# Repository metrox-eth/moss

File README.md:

# MOSS

Cleaner streets, one maker at a time.

> **MOSS kits are coming soon on [TNKR](https://tnkr.ai/).**
> Skip printing and sourcing the parts yourself. **[Join the waitlist →](https://ak4khuvxkya.typeform.com/to/qaKmXNME)** to be notified when kits are available.

**[Build guide](https://www.showrobotics.ai/moss/build/) · [Print parts](https://www.showrobotics.ai/moss/build/#print) · [Bill of materials](BOM.md) · [Download CAD, STL & 3MF](https://github.com/metrox-eth/moss/releases/download/v0.6-r92/MOSS_R92_Mechanical_20261109.zip) · [Software setup](Software.md)**

MOSS is a small litter-picking rover you print and build yourself: a tracked base, a bin on top, an arm derived from the SO-101 with a parallel gripper. It is built in public, with hardware files available for noncommercial builds and improvements.

**Where it stands.** The physical rover drives and demonstrates pick-and-drop motions. Autonomous litter picking and the full field test are not yet demonstrated. The V0.6 / R92 CAD, STL files, BOM and assembly guide are now available.

## Build options

**Base assembly: about $460 in parts.** Includes the chassis and tracks, arm and gripper, motors, servos, control electronics, power system, wrist camera, 2D lidar, wiring and filament. **Only the computer and navigation camera are additional.**

**Choose ONE of the three options below, depending on your budget.** They are alternative computer + navigation-camera configurations for the same rover base. You do not need to buy all three.

| Option | Computer + navigation camera | Additional cost (USD) | Estimated rover total, including the $460 base (USD) |
|---|---|---:|---:|
| **Option 1: higher budget** | Jetson Orin Nano Super + RealSense D455 | about $930 | **about $1,390** |
| **Option 2: mid-range budget** | Raspberry Pi 5 + Hailo AI HAT + Orbbec Gemini 2 | about $740 | **about $1,200** |
| **Option 3: lowest budget, experimental** | Orange Pi Zero 3W (6 GB, $60) + MightyCam ($80) | about $140 | **about $600** |

**Option 1 offers the most computing headroom for the autonomy software being developed.** It does not guarantee autonomous operation: autonomous litter collection has not yet been demonstrated on any of these configurations.

The goal is to bring as much of the stack as possible to smaller, lower-cost hardware. This work involves porting, optimizing and testing features progressively, and **it will take time**. Feature support will depend on what can be ported and validated on each hardware option.

**Option 3 is experimental for now.** Early Orange Pi + MightyCam bench tests are documented in the [experiment folder](experiments/orange-pi-mightycam/); the combination is not yet validated as a complete rover configuration. The [BOM](BOM.md) covers the established configurations.

## What it is made of

- Tracked base, two geared DC motors with encoders, printed TPU tracks, an ESP32-S3 driving the motors.
- A bin you empty by hand at the end of a run.
- An SO-101 arm (open source) with a NormaCore parallel-jaw gripper, widened to a 90 mm grip.
- Two cameras: a depth camera at the nose, a colour camera in the hand.
- A 2D lidar for navigation.
- Software: dimOS for teleop, recording, navigation and manipulation.

I pick up litter by hand on my walks. MOSS is the robot I want next to me doing the same. One less can on the ground.

## News

- 1 November 2026: **[MOSS CORE V0.7 updated](hardware/electronics/moss-core-v0.7/)** — black 82 × 79 mm board, vertical cable headers, larger underside connector labels, a 74 × 71 mm chassis mounting pattern and a new routing layout. Orange Pi assembly clearance and the matched KiCad/BOM/Gerber package are documented. The integrated power supply, current sensing and consolidated motor harness remain. First prototype, not built or tested yet.

- 30 October 2026: **[MOSS CORE V0.7 harness study](hardware/electronics/moss-core-v0.7/harness/)** — a short film, offline 3D viewer, cable routing and a hull prototype with integrated cable-tie mounts. An unbuilt packaging proposal, published for review.

- 28 October 2026: **[Build a custom 3S4P battery for MOSS](hardware/power/custom-3s4p-battery/)** — twelve EVE 21700 cells, illustrated assembly, wiring diagram and parts list. 20 Ah from the cell ratings, 910 g assembled; usable energy and collection runtime still to be measured.
- 27 October 2026: **[Orange Pi + MightyCam experiment](experiments/orange-pi-mightycam/)** — dimOS, YOLO on the NPU and a first memory/load test with simulated rover I/O. Code, cockpit image and the limits of this early bench demo.
- 27 October 2026: **[SO-101 dual-servo shoulder R2: complete upgrade guide](hardware/mechanical/dual-shoulder-r2/)** — editable CAD, two printable parts, screws, assembly, paired-servo setup and testing in one place.
- 24 October 2026: **BOM and print plates updated.** Hoco HB1 four-port hub, GameSir Nova 2 Lite controller, all 38 spacers on one plate, and one tensioner-slider reference (print four). [Updated package](https://github.com/metrox-eth/moss/releases/download/v0.6-r92/MOSS_R92_Mechanical_20261024.zip) · [Print plates](https://www.showrobotics.ai/moss/build/print-plates.html).
- 18 October 2026: **Ready-to-print plates are available.** [H2S: one-piece hull and cover](https://github.com/metrox-eth/moss/releases/download/v0.6-r92/MOSS_V06_R92_H2S_Print_Plates.3mf) or [P1 / P2: split hull and cover](https://github.com/metrox-eth/moss/releases/download/v0.6-r92/MOSS_V06_R92_256mm_Split_Print_Plates.3mf). The [updated package](https://github.com/metrox-eth/moss/releases/download/v0.6-r92/MOSS_R92_Mechanical_20261018.zip) includes both Jetson retaining tabs, grouped STLs with quantities, and both 3MF projects. [Choose your plates](https://www.showrobotics.ai/moss/build/print-plates.html).

- 16 October 2026: **V0.6 / R92 is available.** [Build guide](https://www.showrobotics.ai/moss/build/), [CAD & STL package](https://github.com/metrox-eth/moss/releases/tag/v0.6-r92) and [BOM](BOM.md). One-piece and two-piece hull/cover options, modular computer and camera carriers, and short assembly videos.

- 15 October 2026: [MOSS Core V1D routed PCB draft](hardware/electronics/moss-core-v1d/): integrated audio and switched motor/servo power, published for review. Untested and not approved for fabrication. [V1C critical erratum](hardware/electronics/moss-core-v1d/V1C_CRITICAL_ERRATA.txt): do not fabricate V1C.
- 14 October 2026: [CAD development with Codex](docs/cad-with-codex.md): more battery room, integrated audio, a slimmer hull, a P1S split-hull option and deeper track guides. Images and geometry checks; physical validation is next.
- 3 October 2026: V0.6 makes the hardware modular, Pi or Jetson, RealSense or Gemini. Waitlist open with Tnkr.
- 1 October 2026: V0.5, the release candidate for the open source CAD.
- 26 September 2026: arm and gripper mounted on the prototype.
- 22 September 2026: first drive.

## Friends

OpenAI (Codex Physical Builds), [PCBWay](https://www.pcbway.com/) (custom PCB prototyping), [Dimensional](https://x.com/dimensionalos) (dimOS), [NormaCore](https://x.com/norma_core_dev) (gripper), [Tnkr](https://x.com/tnkrdotai) (kits and guide), [Dirac Robotics](https://x.com/diracrobotics) (calibrated simulation), [microduck-lab](https://github.com/jonathanhawkins/microduck-lab) (reinforcement learning). We help each other.

## Supporters

People who put a spool of filament in the rover every month: [Richard Burton](https://github.com/ricburton). It goes into parts the same week. You can join them on [GitHub Sponsors](https://github.com/sponsors/metrox-eth).

## Simulation and autonomy, work in progress

The current **[MOSS V0.6 / R92 MuJoCo model](simulation/mujoco/)** lives in this repository, with its XML, meshes, viewer and tests. It includes the released assembly geometry, an articulated arm and coupled gripper, and an idealized base that can drive and turn. It runs locally without Jev or an API key. Start with the **[simulation guide](simulation/mujoco/README.md)** or **[model files](simulation/mujoco/model/)**.

This is a preliminary development model: traction, servo dynamics, camera geometry and sim-to-real accuracy remain uncalibrated. Dirac Robotics is helping build the calibrated simulation; Dimensional is working on a navigation arena, and microduck-lab is trying reinforcement learning. The earlier recorded Jev demonstration remains in [moss-jev](https://github.com/metrox-eth/moss-jev) as historical work.

## Come and build

Ask anything, tell us what we are doing wrong, it helps the next builder: [Discord](https://discord.com/invite/x2MeNmgveT). The build, as it happens: [@metrox_eth](https://x.com/metrox_eth). The story so far, in a few moments: [STORY.md](STORY.md). How data from many rovers gets pooled: [docs/data.md](docs/data.md).

## Safety

This is a prototype with a lithium battery and no certified protection. Put it on blocks for the first run. Build at your own risk.

## License

Code remains under Apache-2.0. From **1 November 2026**, the current distribution of MOSS-authored hardware designs is offered under **[CC BY-NC-SA 4.0](LICENSE-HARDWARE)**: attribution, noncommercial use and ShareAlike. Documentation and media remain under CC BY 4.0.

Earlier CERN-OHL-S-2.0 distributions retain the rights already granted with those copies. Third-party material keeps its own licence, including the KiCad library licence and exception. See [NOTICE](NOTICE) for scope and attribution.

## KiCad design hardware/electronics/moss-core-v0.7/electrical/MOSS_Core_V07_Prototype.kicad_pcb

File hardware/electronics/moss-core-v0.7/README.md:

# MOSS CORE V0.7 — Prototype

This is my first custom PCB for **MOSS, the litter-picking rover**, designed with Codex and KiCad. I am publishing the editable design so people with electronics experience can help review it before the first assembled prototypes are tested.

**Updated 2 November 2026: component reference markings.** The matched files below describe the current layout for PCBWay engineering review. This is still the first, unbuilt prototype; hardware revision letters are reserved for fabricated boards.

## What changed

The current update adds printed component references while keeping the existing numbering. It changes the legends only: the circuit, components, copper, drill pattern, connector pinouts and placements remain the same as the power/rearm design. See [reference markings and verification scope](SILKSCREEN_UPDATE.md), including the U15 dense-area exception and its assembly locator.

The preceding electrical update is retained:

- **Supply recovery now requires a fresh arm pulse.** A hardware latch prevents held enable/PWM levels from automatically reopening the command gates after a qualified actuator-supply fault. GPIO1 provides the arm pulse; GPIO2 reads back the latch. The firmware must support this interface.
- **Logic-regulator transient response:** C170 adds the 6.8 pF feedforward capacitor recommended by TI for the existing feedback divider. The nominal logic voltage remains 3.384 V. Its response under load still needs measurement.
- **Targeted corner cleanup:** actual right-angle bends were chamfered on selected USB, audio, encoder and ADC paths. Track orientation and bend angle are now checked separately. Existing motor-power widths and shunt connections are preserved.

The 82 × 79 mm black board, 74 × 71 mm Core fixing pattern, Orange Pi mounting pattern, vertical connectors and harness pinout are retained. The updated hull already follows these fixing centres. This remains the first, unbuilt prototype, without a new physical revision letter.

See [power behavior, firmware rearming and bench checks](POWER_AND_REARM.md). The latch inhibits motor command signals and new servo UART transmission; it does not certify servo power-up behavior or EMI immunity.

The native design, assembly inventory and fabrication outputs below form one matched set for engineering review.

## What the board does

The four-layer board has an **82 × 79 mm rounded rectangular outline**, without protruding ears. The chassis mounting pattern is now 74 × 71 mm; Orange Pi standoff positions are unchanged. It combines an ESP32-S3 controller, a powered half-duplex serial-servo interface, Cytron control and encoder interfaces, left/right motor-current sensing, battery-voltage measurement, an I2S speaker amplifier and an integrated Orange Pi power supply. The Cytron motor driver and USB hub remain external.

The arm uses one daisy-chain connector for the standard six-servo configuration, or seven with the optional twin shoulder. The selected connector and the actual common power harness still need aggregate-current qualification. Core firmware needs its own port and commissioning; this is not a drop-in replacement for the existing controller firmware.

The current design includes two chassis-fan outputs, corrected connector legends, the six-position stop connector with two deliberately unwired positions, and a compact soldered **Littelfuse 08853.15DR, 3.15 A**, on the Orange Pi supply input branch. F1 has no separate holder, cartridge or cover; replacement requires soldering. F2/F3 are separate 1 A audio/fan branch fuses, and the external 15 A pack fuse remains required.

The fan outputs carry fused 3S battery voltage, up to 12.6 V, rather than regulated 12 V. Their combined 0.2 A running current is an estimate, not a measurement. See the [connector guide](CONNECTORS.md) and [F1 selection evidence](evidence/F1_SELECTION.md).

## Orange Pi assembly clearance

The combined [mechanical review](evidence/MECHANICAL_REVIEW.json) uses **20 mm Orange Pi standoffs**, a CAD mounting height, and the measured **16 mm total Orange Pi/cooler height**. The [updated hull prototype](https://github.com/metrox-eth/moss/tree/main/hardware/mechanical/moss-v0.7-hull) uses the new **74 × 71 mm Core fixing pattern**, with its own geometry checks and editable source. The earlier mechanical review remains evidence for the upper stack; its request to update the hull posts is addressed by this separate hull update. The component bodies clear the Orange Pi and four standoffs, including a 6 mm diameter standoff reservation. The conservative vertical gap from the highest component beneath the Orange Pi to its lowest underside feature is **4.15 mm**.

The mated-connector and wire checks use supplier dimensions where available and declared clearance envelopes elsewhere. **Route J2's wires rearward and J3's wires leftward, away from the Orange Pi, before bringing them upward.** A straight, expanded vertical bundle reservation at these two ports intersects the Orange Pi CAD. This is an assembly routing condition; the exact cable and connector tolerances still need checking on the first prototype. The cooler's lateral shape was not supplied, so its final cable clearance also needs checking.

The [outward cable-route check](preview/CABLE_CLEARANCE_ROUTES.png) uses declared 5 mm bundles with 10 mm bend radii. These example routes clear the supplied Pi, standoffs and hull CAD, plus the conservative cooler envelope; they are clearance reservations, not manufacturing drawings for a finished harness. [Intersection results](evidence/CABLE_CLEARANCE_ROUTES.json).

The [mounting table](MOUNTING.md) gives the current chassis fixing pattern. The [update equivalence report](evidence/UPDATE_EQUIVALENCE.json) identifies the preserved geometry and prior evidence that remains applicable. The [730-pin consistency check](evidence/DESIGN_CONTRACT.json), [routing-angle check](evidence/TRACK_ANGLES.json) and [rearm state-model results](evidence/LOGIC_REARM_MODEL.json) cover the updated files. These are static and modeled checks, not powered or thermal test results.

## Harness packaging study

The [harness study](https://github.com/metrox-eth/moss/tree/main/hardware/electronics/moss-core-v0.7/harness) follows the current integrated-power board and vertical connectors. Each motor uses one six-wire cable to J3/J4. A nine-wire link at J2 groups the Cytron control and motor-output circuits; J11 retains its separate supply. The model includes the updated hull fixings, five cable-tie bridges and the divider notch. The package contains current CAD, an offline viewer, wiring schedules and a prototype RFQ. The harness model retains the earlier board body; connector geometry and pin assignments are unchanged by this update. The latest internal-component views are the two images above. The older film is historical and is not evidence for this layout. Physical fit and electrical operation remain first-prototype checks.

## Assembly review

A [focused mask/paste and BOM review](evidence/assembly_review/README.md) checked the current-sense shunts and amplifiers. Their apertures remain separate; the later legend update preserves these openings and the production CSV. A classified BOM view makes semiconductors, passives and connectors easier to inspect. Stencil and reflow-process confirmation remains with PCBWay.

## Firmware and commissioning

The separate [Core V0.7 commissioning firmware](https://github.com/metrox-eth/moss/tree/main/firmware/core-v0.7) reuses the current MDD10A ramp and encoder code. It implements the new rearm interface, USB commands/telemetry, battery and motor-current readings, half-duplex Feetech communication including group writes, and an I²S speaker test. The existing V0.6 controller remains the tested rover target.

The ESP32-S3 build passes with zero compiler warnings. Shared-code host tests and a separate review cover faults, stale commands, timing, measurements and serial behavior. [Evidence and source hashes](evidence/FIRMWARE_CROSSCHECK.json). No firmware has been flashed to this new board, and no powered operation or EMI result is claimed. Its commissioning console is explicit; this is not yet a drop-in dimOS controller/arm adapter.

## Download and inspect

- [Complete prototype review package](delivery/MOSS_CORE_V07_PROTOTYPE_REVIEW_20261102_SILKSCREEN.zip).
- [KiCad project](electrical/MOSS_Core_V07_Prototype.kicad_pro), [PCB](electrical/MOSS_Core_V07_Prototype.kicad_pcb) and [root schematic](electrical/MOSS_Core_V07_Prototype.kicad_sch).
- [Physical-pin circuit contract](electrical/circuit.json), local symbols and footprints in `electrical/`.
- [Grouped component BOM](delivery/assembly/MOSS_CORE_V07_PROTOTYPE_BOM.csv) and [placement file](delivery/assembly/MOSS_CORE_V07_PROTOTYPE_POSITIONS.csv): **216 placed components, 99 purchase articles**. The native board also contains mounting holes and test pads, for 230 footprints total.
- [Gerbers and drills](delivery/MOSS_CORE_V07_PROTOTYPE_GERBERS_20261102_SILKSCREEN.zip), with [fabrication notes](delivery/fabrication/FABRICATION_NOTES.txt) and [assembly notes](delivery/assembly/ASSEMBLY_NOTES.txt).
- [File hashes](MANIFEST.json), [check results](evidence/CHECKS.json) and [publication provenance](evidence/PUBLICATION_NOTES.json).

Use KiCad 10. Open the project from `electrical/` so `${KIPRJMOD}` resolves its local libraries and models. Preserve the native-board model settings when updating footprints: some library defaults reference KiCad's installed models. Several custom models are visual approximations, not manufacturer mating CAD. The previews add a simple U60 body and manufacturer-based IC markings, with the ESP shield left unmarked, documented in [visual provenance](preview/VISUAL_PROVENANCE.json); the native PCB is unchanged.

The native candidate PCB is identified by:

```text
SHA-256: 4f456f0563e9dc5a3b7cbab98eaa8d9f24485d14dc79a7656af5ab04b983b6b1
```

## Community review welcome

**Not fabricated or hardware-qualified yet.** The recorded [ERC](evidence/ERC.json) has zero violations. The [PCB DRC](evidence/DRC.json), under the saved project rules, has zero errors, zero missing connections and zero schematic-parity issues. Two bounded warnings are documented in the check report: a retained free copper tip on the battery branch, and a tiny C21 silkscreen clip. The latter is removed from the production ink by the explicit solder-mask subtraction during Gerber export; it does not change copper or drills. These are static checks, not powered test results.

I would especially welcome review of:

- Exact component/pin/footprint matching and connector mating/polarity.
- Power distribution, conductor sizing, return paths, decoupling and routing.
- Integrated-converter startup, ripple and stability with the existing output capacitance, load transients, fuse coordination and thermal behavior.
- The shared servo connector/harness current, actuator-cutoff behavior and motor regeneration/BMS interactions.

The new motor paths use the supplier data for the 90:1 / 110 rpm motors (up to 1 A rated and 2.3 A stall at 12 V), rather than the Cytron's 10 A channel headline. This quotation requests 1 oz copper on all four layers. Load/thermal tests and fault-protection coordination remain necessary; a clean DRC does not establish those ratings.

These remain open design and bench-validation topics. The fan connector identity/current and stop-button contact arrangement also need physical confirmation. No firmware or real-load test result is implied by the views or static checks.

Please [open an issue](https://github.com/metrox-eth/moss/issues) with **MOSS CORE V0.7 Prototype**, the component/net reference, and the relevant datasheet or calculation. Corrections and practical suggestions are very welcome.

## Editing and re-export

Edit the native KiCad design in this folder. Run `python3 tools/check_rearm_logic.py --design . --output evidence/LOGIC_REARM_MODEL.json` after regenerating the netlist to check the rearm state model. Update the circuit contract and assembly BOM when components change. `python3 tools/export_package.py` runs the native checks and regenerates the delivery files. It stops on errors, missing connections, parity differences or an unexpected assembly inventory. `--reuse-checks` requires every recorded design-file hash to match the successful checks. Review the results before manufacturing or powered tests.

## License and provenance

From **1 November 2026**, the current distribution of MOSS-authored hardware design files is offered under **[CC BY-NC-SA 4.0](LICENSE-HARDWARE)**: attribution, noncommercial use and ShareAlike. This covers the PCB design, fabrication outputs and MOSS-authored wiring/harness designs.

Code remains under Apache-2.0; documentation and media remain under CC BY 4.0. Bundled KiCad library collections retain their [CC BY-SA 4.0 licence and KiCad Libraries Exception](KiCad_Libraries_LICENSE.md), and other third-party material keeps its own terms. See [NOTICE](NOTICE).

Earlier copies and releases distributed under CERN-OHL-S-2.0 retain their original grants. This notice does not withdraw or retroactively replace those rights.

Supplier correspondence, account/order information and unrelated workshop files are excluded. Local provenance paths in reports were converted to package-relative paths. File hashes identify each submitted design and its matching fabrication/assembly data. Earlier checks retain their original hashes and are identified as baseline evidence where applicable.

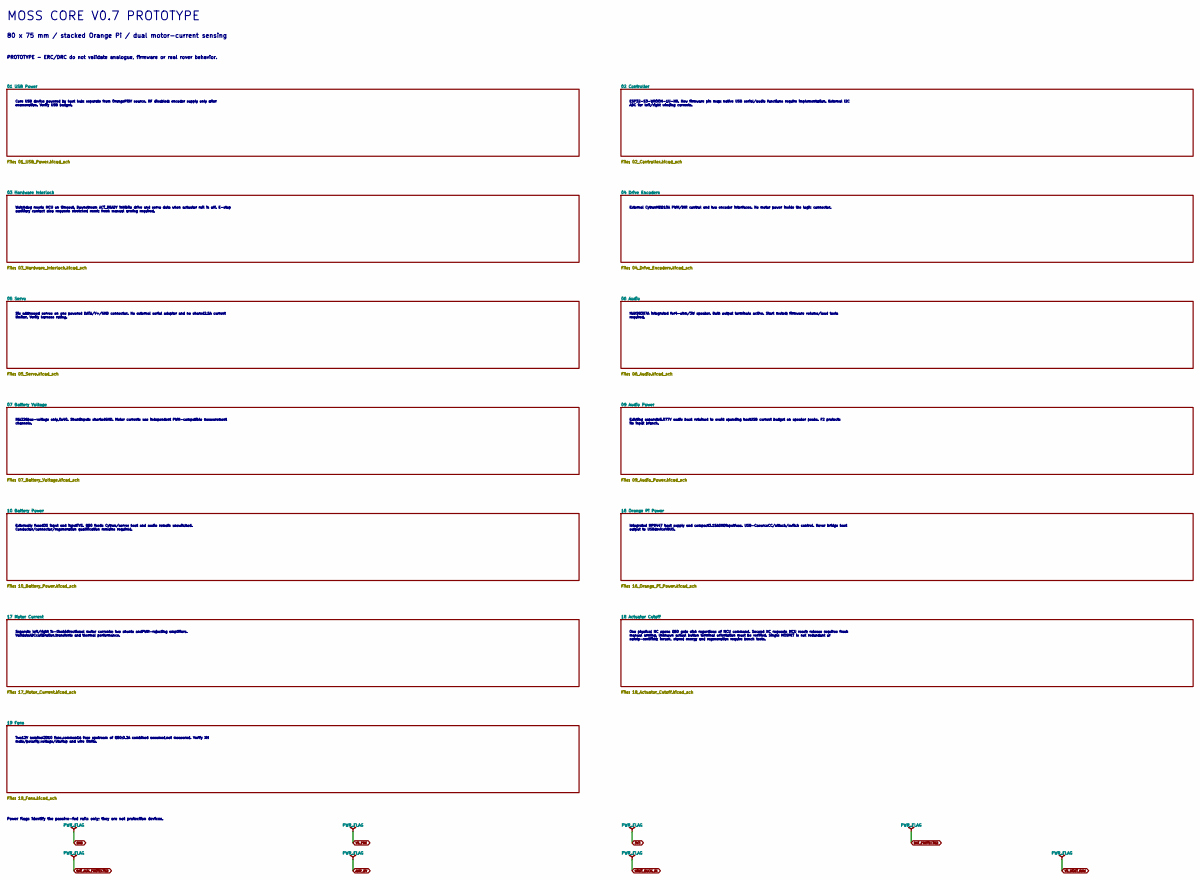
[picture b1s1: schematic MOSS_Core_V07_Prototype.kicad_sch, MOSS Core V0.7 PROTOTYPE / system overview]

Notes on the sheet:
MOSS CORE V0.7 PROTOTYPE
80 x 75 mm / stacked Orange Pi / dual motor-current sensing
PROTOTYPE - ERC/DRC do not validate analogue, firmware or real rover behavior.
Core USB device powered by host hub; separate from OrangePi5V source. RF disabled; encoder supply only after enumeration. Verify USB budget.
ESP32-S3-WROOM-1U-N8. New firmware pin map; native USB serial/audio functions require implementation. External I2C ADC for left/right winding currents.
Watchdog resets MCU on timeout. Downstream ACT_READY inhibits drive and servo data when actuator rail is off. E-stop auxiliary contact also requests stretched reset; fresh manual arming required.
External CytronMDD10A PWM/DIR control and two encoder interfaces. No motor power inside the logic connector.
Six addressed servos on one powered DATA/V+/GND connector. No external serial adapter and no shared2.5A current limiter. Verify harness rating.
MAX98357A integrated for4-ohm/3W speaker. Both output terminals active. Start muted; firmware volume/load tests required.
INA226bus-voltage only,0x40. Shuntinputs shortedGND. Motor currents use independent PWM-compatible measurement channels.
Existing separate5.077V audio buck retained to avoid spending hostUSB current budget on speaker peaks. F2 protects its input branch.
Externally fused3S input and inputTVS. Q50 feeds Cytron/servo; host and audio remain unswitched. Conductor/connector/regeneration qualification remains required.
Integrated MP9447 host supply and compact3.15ASMDinputfuse. USB-CsourceCC/attach/switch control. Never bridge host output to USBdeviceVBUS.
Separate left/right in-linebidirectional motor currents; two shunts andPWM-rejecting amplifiers. ValidateADCcalibration,transients and thermal performance.
One physical NC opens Q50 gate sink regardless of MCU command. Second NC requests MCU reset; release requires fresh manual arming. Unknown actual button terminal orientation must be verified. Single MOSFET is not redundant or safety-certified; inrush, stored energy and regeneration require bench te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
Two12V nominal3010 fans,common1A fuse upstream of Q50;0.2A combined assumed,not measured. Verify XH mate/polarity,voltage/startup and wire limits.
Power flags identify the passive-fed rails only; they are not protection devices.

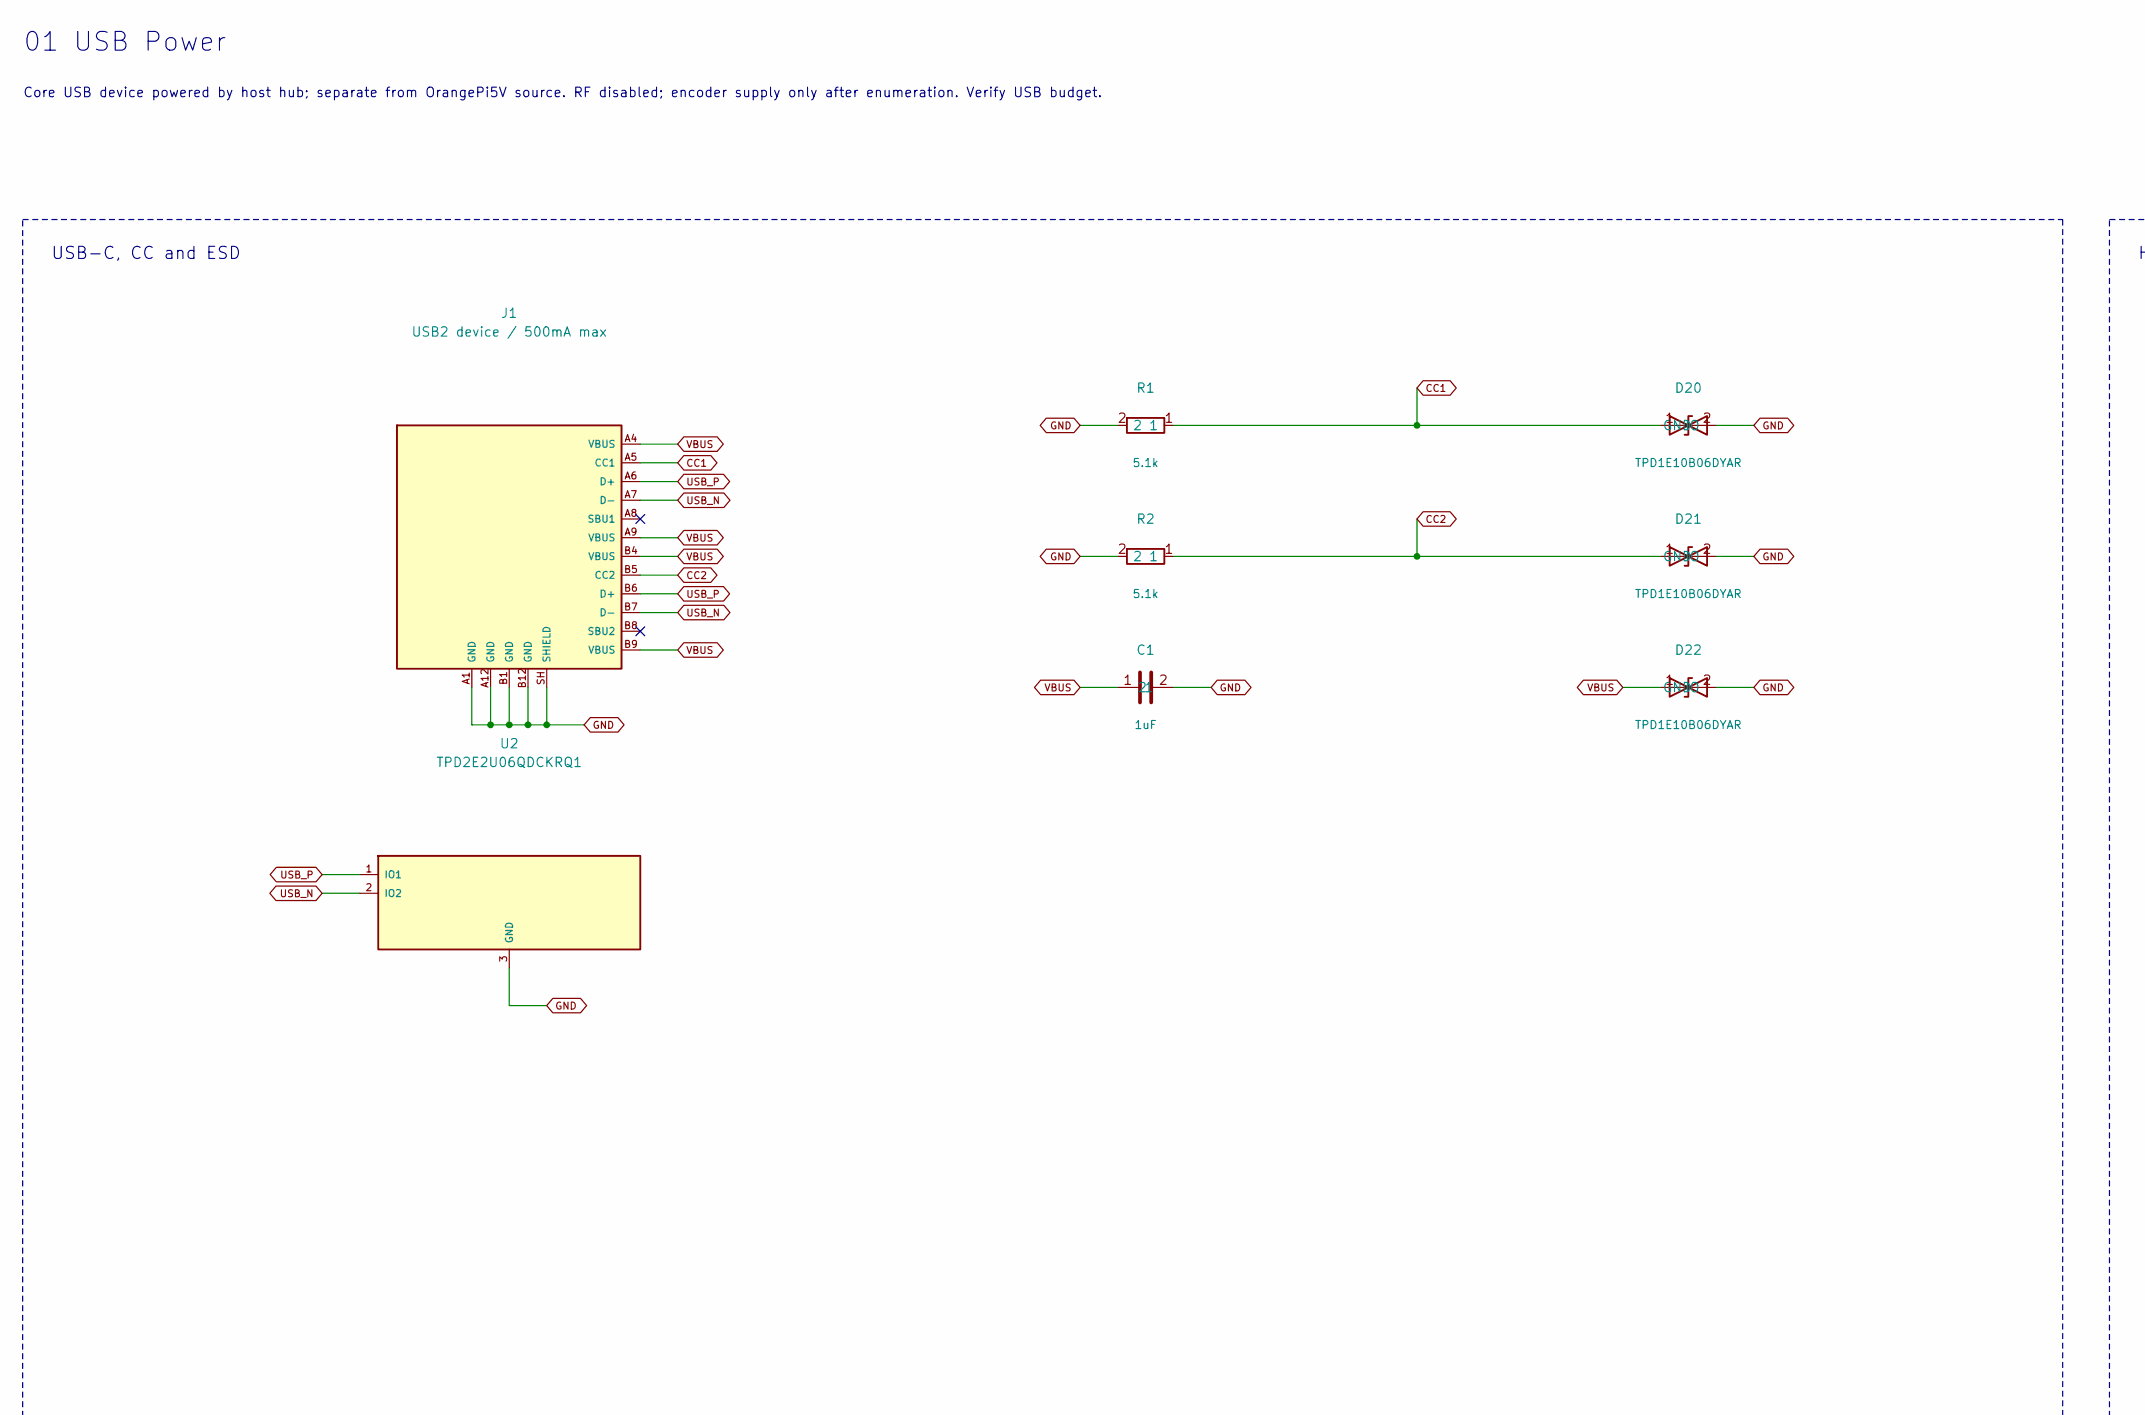
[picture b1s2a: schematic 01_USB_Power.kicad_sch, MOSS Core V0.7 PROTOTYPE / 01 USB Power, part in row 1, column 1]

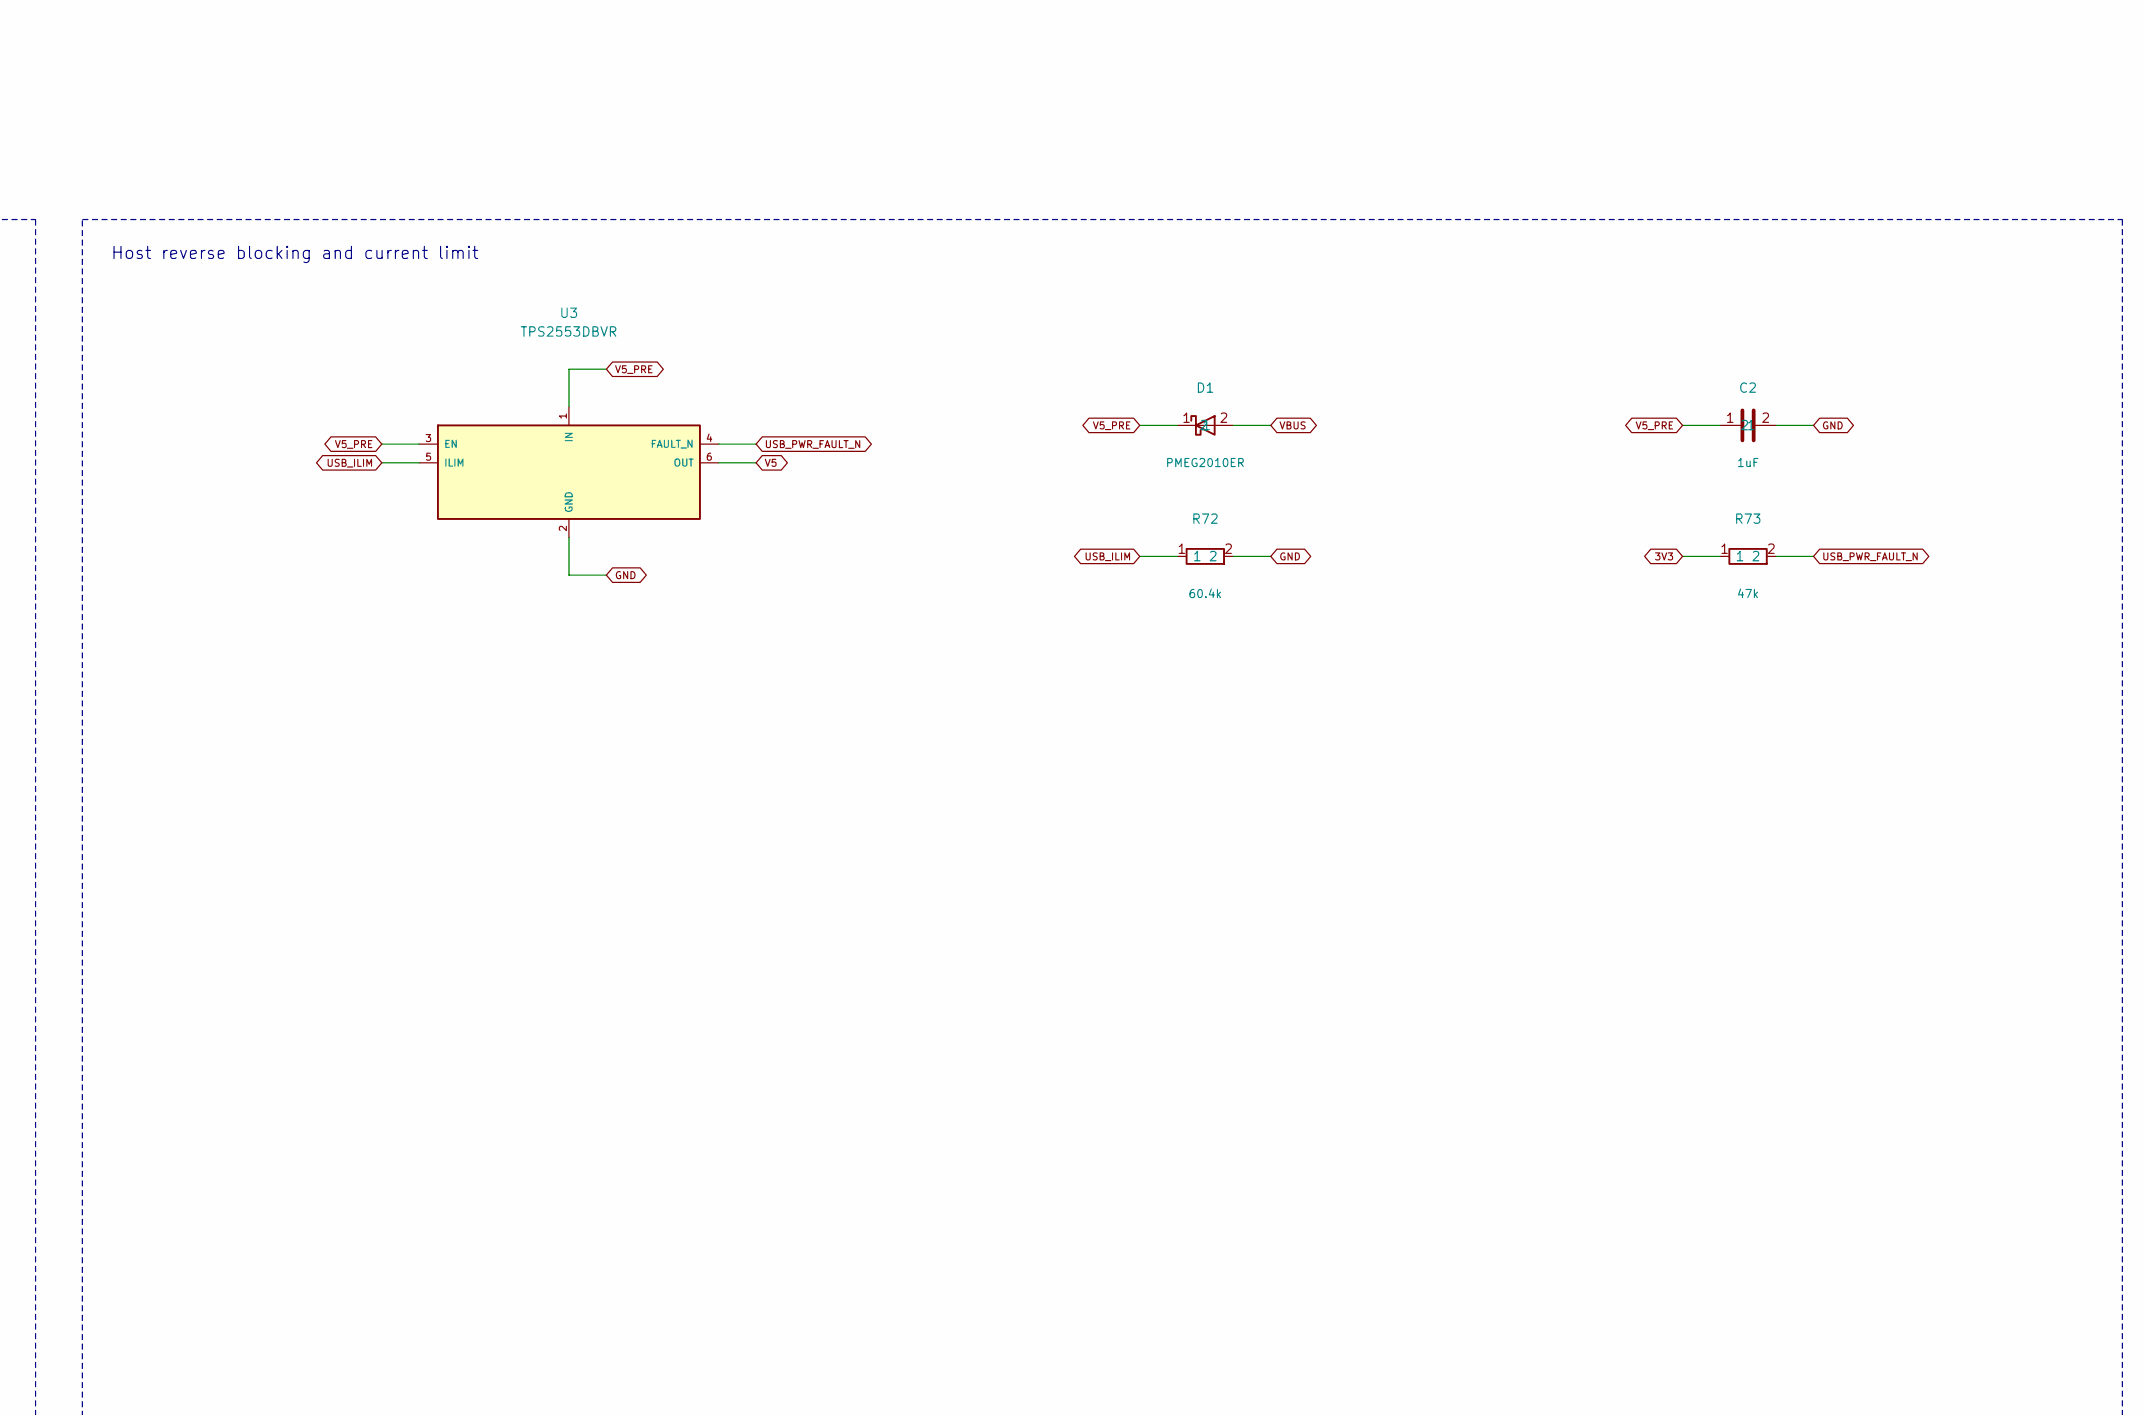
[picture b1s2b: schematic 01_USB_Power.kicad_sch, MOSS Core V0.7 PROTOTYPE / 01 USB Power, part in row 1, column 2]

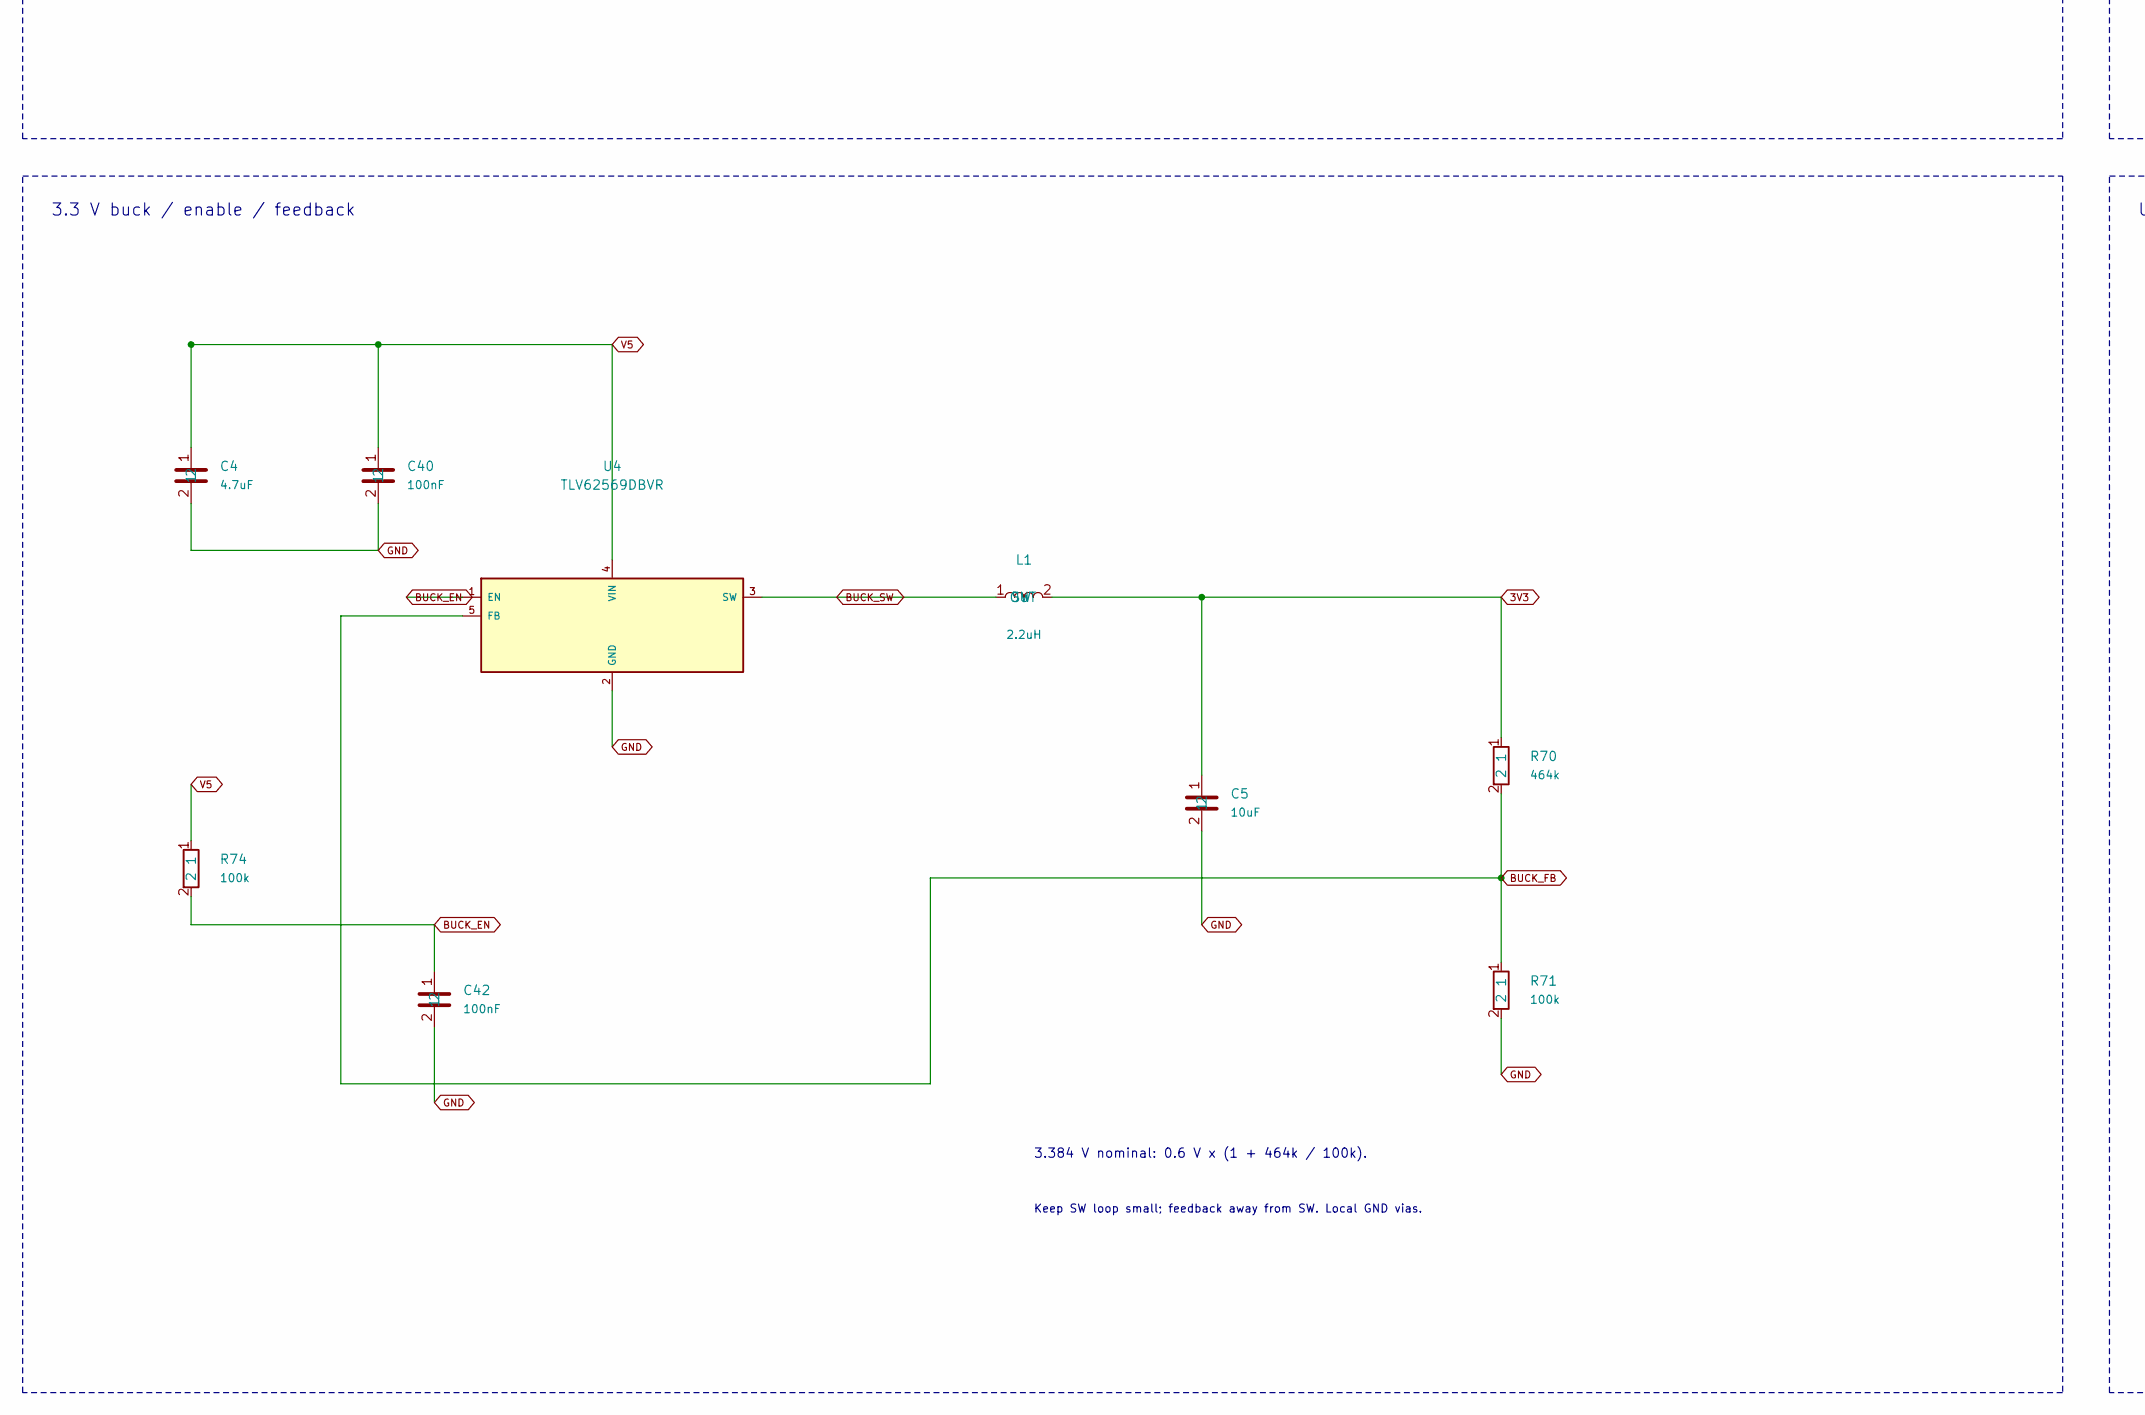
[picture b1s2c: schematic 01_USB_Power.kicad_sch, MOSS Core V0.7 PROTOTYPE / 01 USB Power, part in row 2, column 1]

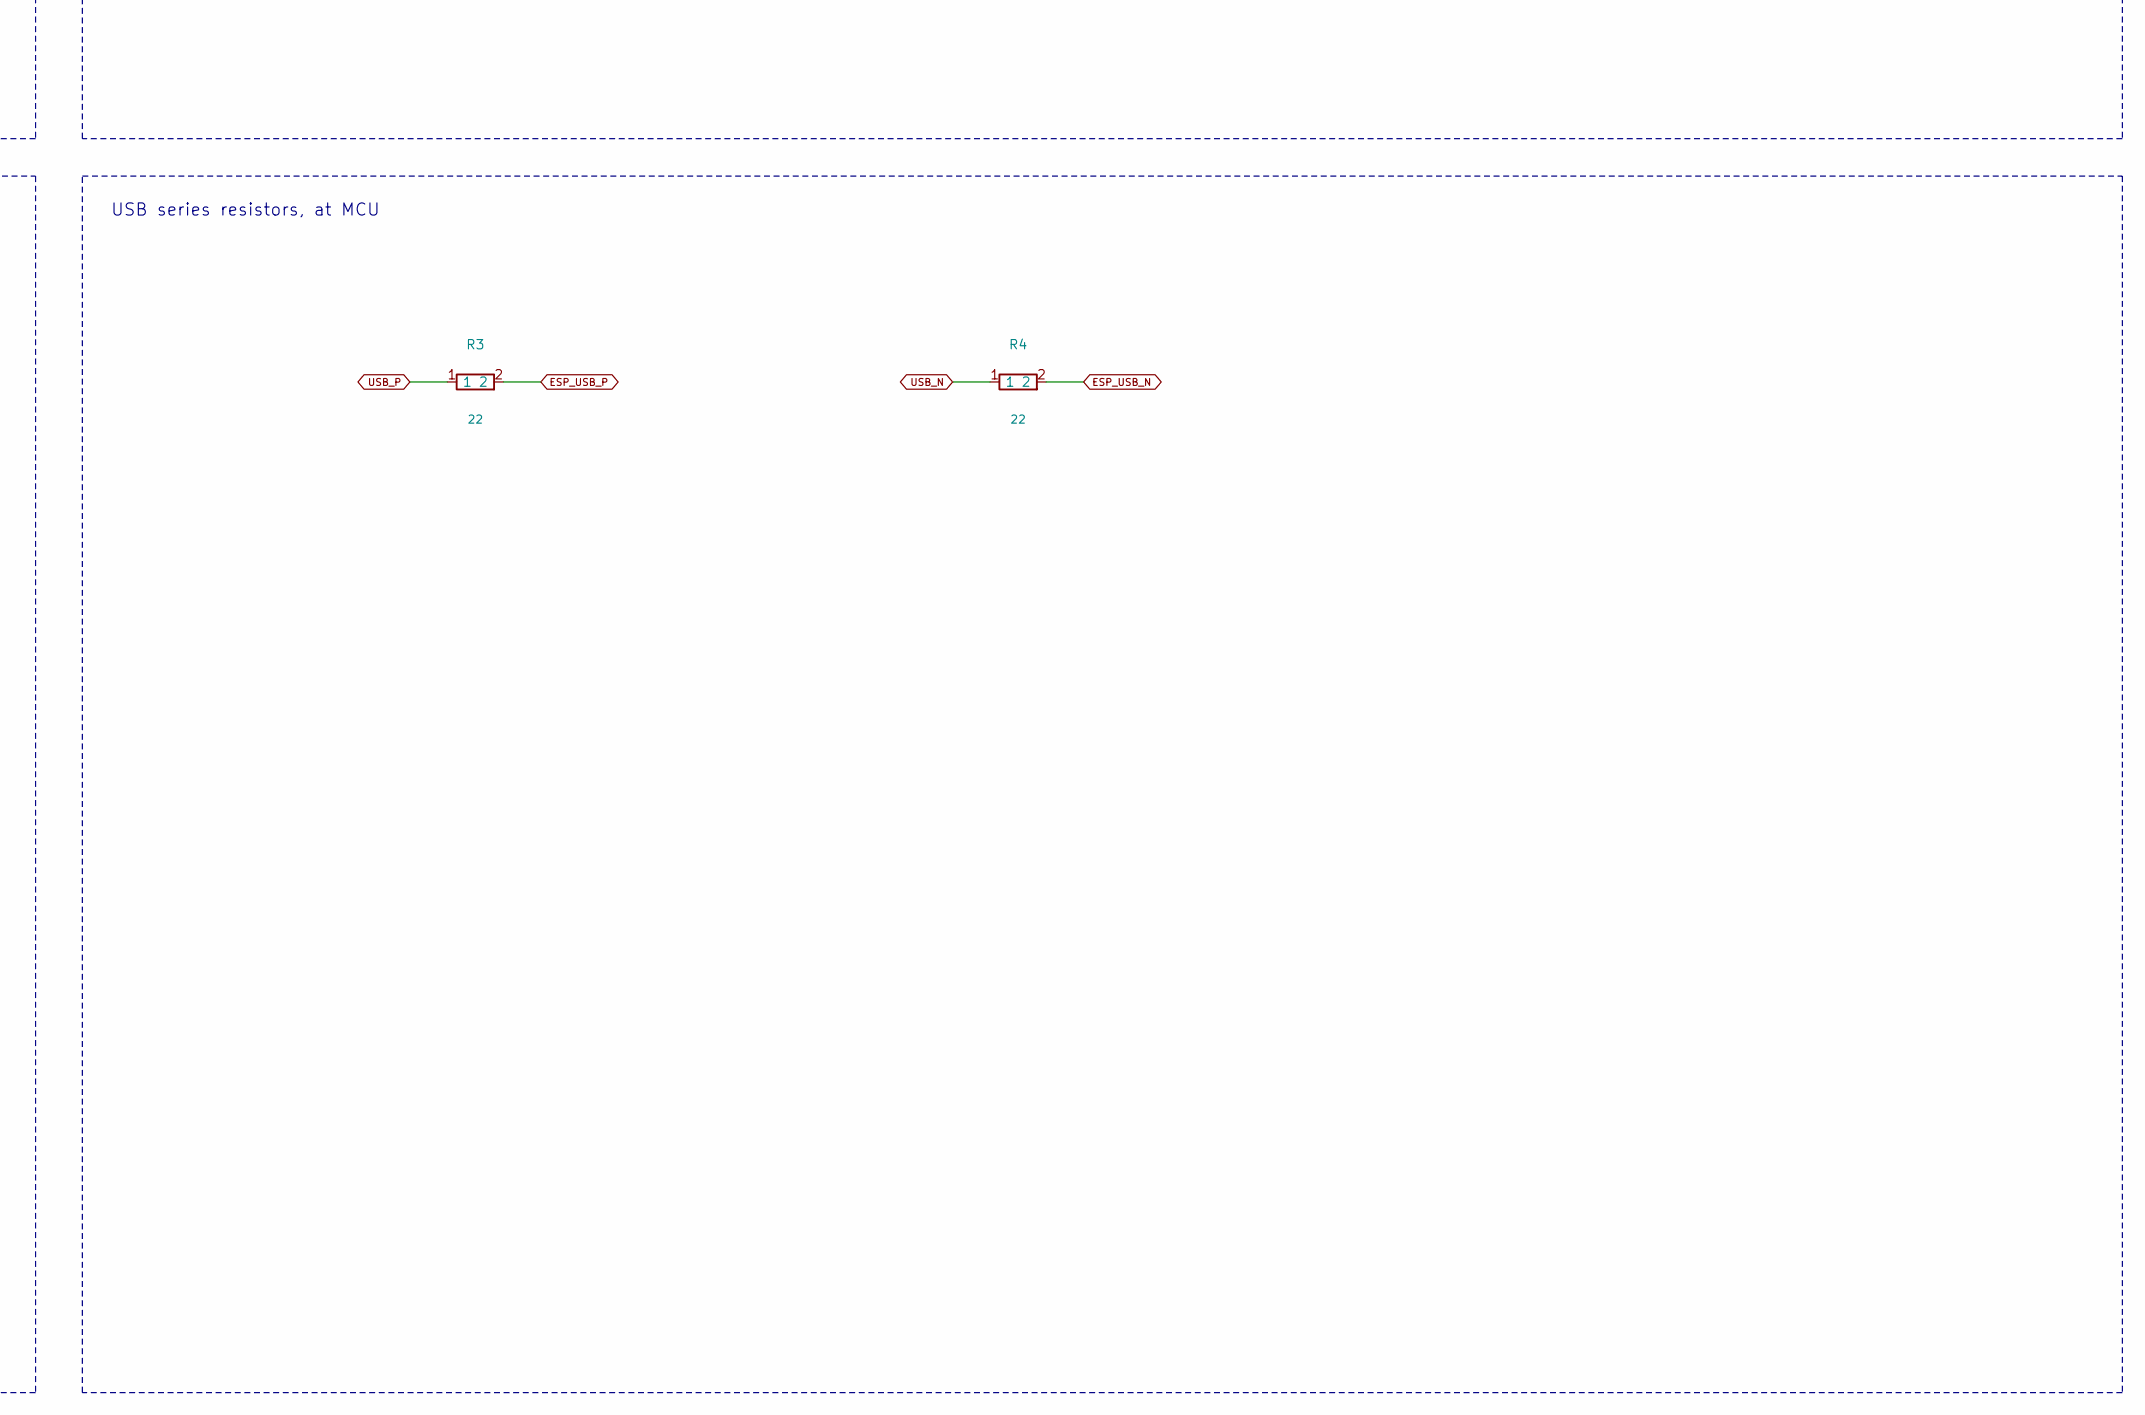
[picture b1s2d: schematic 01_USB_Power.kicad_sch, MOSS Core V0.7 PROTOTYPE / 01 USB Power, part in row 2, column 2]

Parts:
C1, C2: 1uF; Capacitor_SMD_C_0603_1608Metric; MPN GRM188R61A105KA61D
C4: 4.7uF; Capacitor_SMD_C_0805_2012Metric; MPN GRM21BR71A475KA73L
C5: 10uF; Capacitor_SMD_C_0805_2012Metric; MPN GRM21BR71A106KA73L
C40, C42: 100nF; Capacitor_SMD_C_0603_1608Metric; MPN GRM188R71C104KA01D
D1: PMEG2010ER; Diode_SMD_Nexperia_CFP3_SOD-123W; MPN PMEG2010ER,115
D20, D21, D22: TPD1E10B06DYAR; Diode_SMD_D_SOD-523; MPN TPD1E10B06DYAR
J1: USB2 device / 500mA max; Connector_USB_USB_C_Receptacle_GCT_USB4105-xx-A_16P_TopMnt_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; MPN USB4105-GF-A
L1: 2.2uH; Inductor_SMD_L_Coilcraft_XAL4020-XXX; MPN XAL4020-222MEC
R1, R2: 5.1k; Resistor_SMD_R_0603_1608Metric; MPN RC0603FR-075K1L
R3, R4: 22; Resistor_SMD_R_0402_1005Metric; MPN RC0402FR-0722RL
R70: 464k; Resistor_SMD_R_0603_1608Metric; MPN RT0603BRD07464KL
R71: 100k; Resistor_SMD_R_0603_1608Metric; MPN RT0603BRD07100KL
R72: 60.4k; Resistor_SMD_R_0603_1608Metric; MPN RC0603FR-0760K4L
R73: 47k; Resistor_SMD_R_0603_1608Metric; MPN RC0603FR-0747KL
R74: 100k; Resistor_SMD_R_0603_1608Metric; MPN RC0603FR-07100KL
U2: TPD2E2U06QDCKRQ1; Package_TO_SOT_SMD_SOT-323_SC-70; MPN TPD2E2U06QDCKRQ1
U3: TPS2553DBVR; Package_TO_SOT_SMD_SOT-23-6; MPN TPS2553DBVR
U4: TLV62569DBVR; Package_TO_SOT_SMD_SOT-23-5; MPN TLV62569DBVR

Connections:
3V3: C5.1, L1.2 (OUT), R70.1, R73.1; also elsewhere on the board
BUCK_EN: C42.1, R74.2, U4.1 (EN)
BUCK_FB: R70.2, R71.1, U4.5 (FB); also elsewhere on the board
BUCK_SW: L1.1 (SW), U4.3 (SW)
CC1: D20.1 (IO), J1.A5 (CC1), R1.1
CC2: D21.1 (IO), J1.B5 (CC2), R2.1
ESP_USB_N: R4.2; also elsewhere on the board
ESP_USB_P: R3.2; also elsewhere on the board
GND: C1.2, C2.2, C4.2, C5.2, C40.2, C42.2, D20.2 (GND), D21.2 (GND), D22.2 (GND), J1.A1 (GND), J1.A12 (GND), J1.B1 (GND), J1.B12 (GND), J1.SH (SHIELD), R1.2, R2.2, R71.2, R72.2, U2.3 (GND), U3.2 (GND), U4.2 (GND); also elsewhere on the board
USB_ILIM: R72.1, U3.5 (ILIM)
USB_N: J1.A7 (D-), J1.B7 (D-), R4.1, U2.2 (IO2)
USB_P: J1.A6 (D+), J1.B6 (D+), R3.1, U2.1 (IO1)
USB_PWR_FAULT_N: R73.2, U3.4 (FAULT_N); also elsewhere on the board
V5: C4.1, C40.1, R74.1, U3.6 (OUT), U4.4 (VIN)
V5_PRE: C2.1, D1.1, U3.1 (IN), U3.3 (EN)
VBUS: C1.1, D1.2, D22.1 (IO), J1.A4 (VBUS), J1.A9 (VBUS), J1.B4 (VBUS), J1.B9 (VBUS)

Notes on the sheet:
01 USB Power
Core USB device powered by host hub; separate from OrangePi5V source. RF disabled; encoder supply only after enumeration. Verify USB budget.
USB-C, CC and ESD
Host reverse blocking and current limit
3.3 V buck / enable / feedback
3.384 V nominal: 0.6 V x (1 + 464k / 100k).
Keep SW loop small; feedback away from SW. Local GND vias.
USB series resistors, at MCU
